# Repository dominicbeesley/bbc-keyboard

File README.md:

# bbc-keyboard
A bbc micro external keyboard

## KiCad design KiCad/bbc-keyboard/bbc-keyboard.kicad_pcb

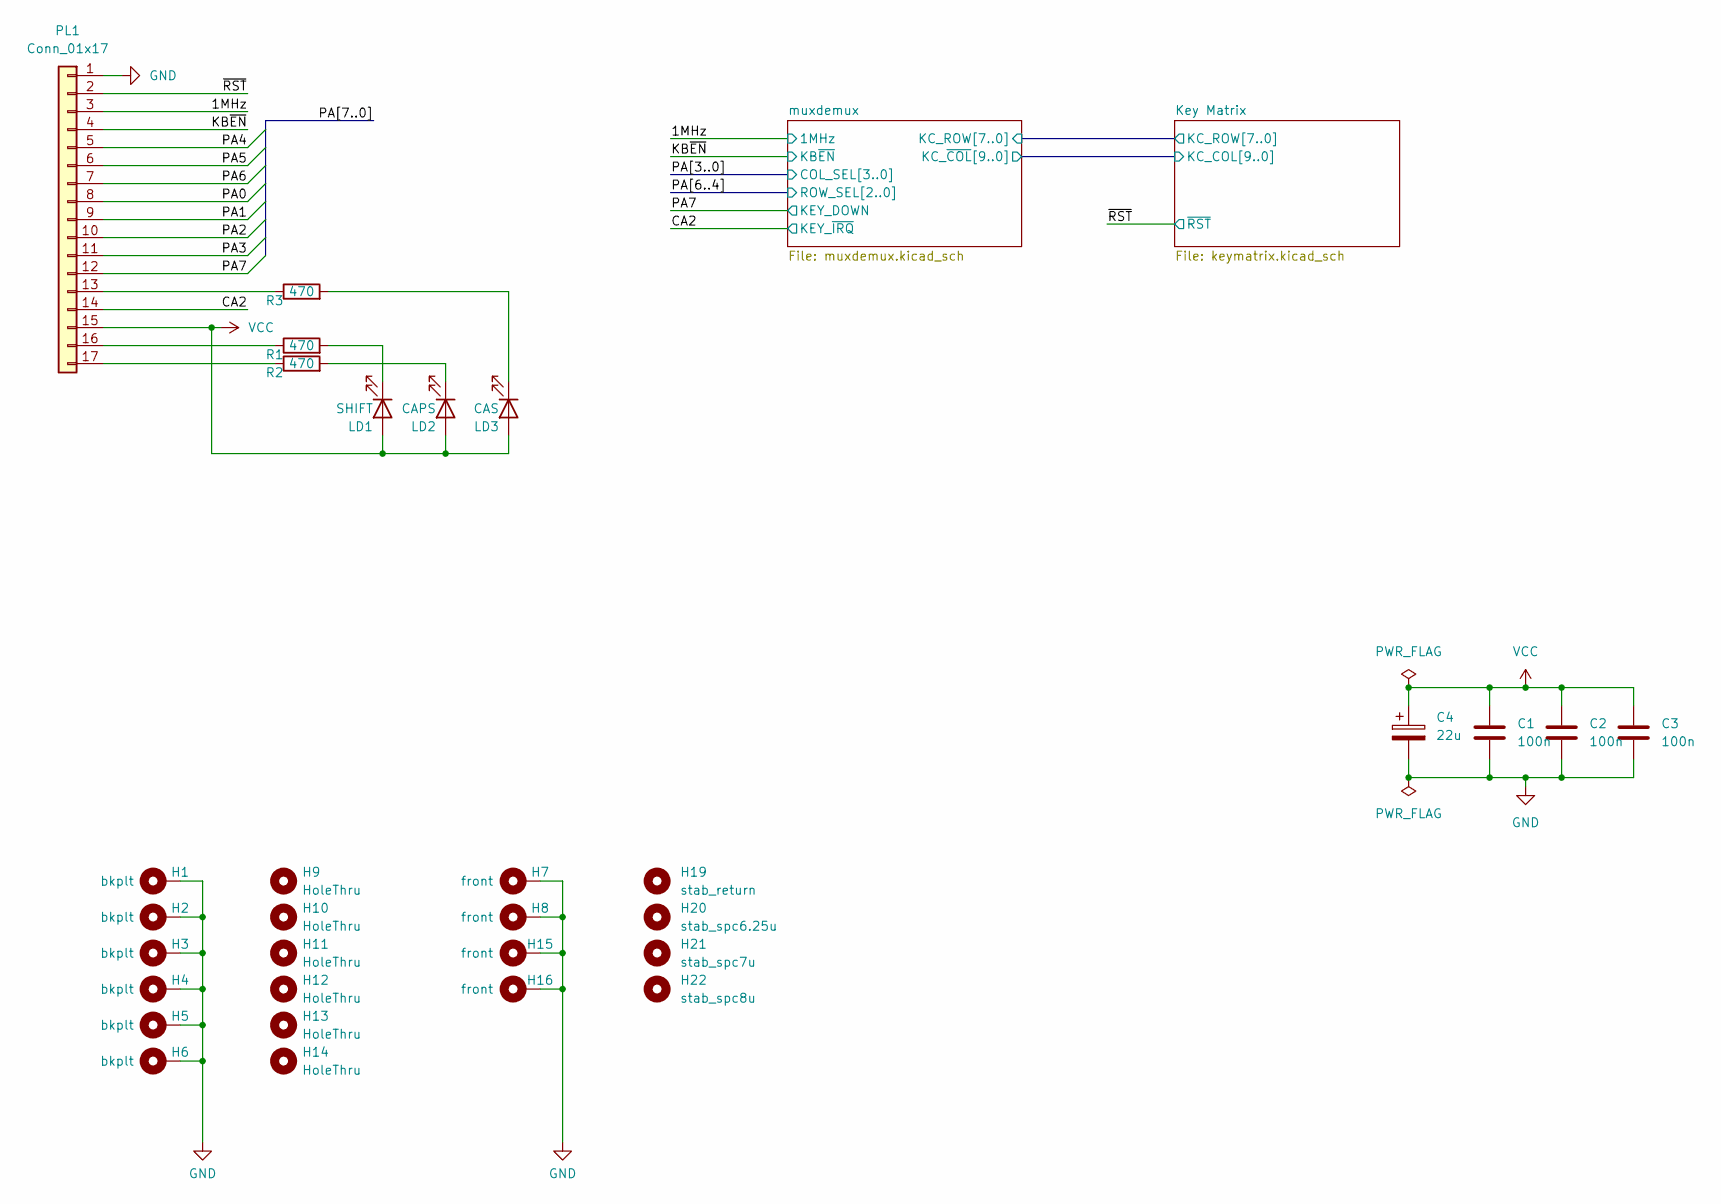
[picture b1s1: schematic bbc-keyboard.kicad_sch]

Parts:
C1, C2, C3: 100n; C_Disc_D9.0mm_W2.5mm_P5.00mm
C4: 22u; CP_Radial_D5.0mm_P2.00mm
H1, H2, H3, H4, H5, H6: bkplt; MountingHole_3.2mm_M3_DIN965_Pad
H7, H8: front; MountingHole_3.2mm_M3_DIN965_Pad
H9, H10, H11, H12, H13, H14: HoleThru; SquareHole_6.5mm
H15, H16: front; MountingHole_2.7mm_M2.5_DIN965_Pad
H19: stab_return; Stabilizer_Cherry_MX_2.00u
H20: stab_spc6.25u; Stabilizer_Cherry_MX_6.25u
H21: stab_spc7u; Stabilizer_Cherry_MX_7.00u
H22: stab_spc8u; Stabilizer_Cherry_MX_8.00u
LD1: SHIFT; LED_D5.0mm
LD2: CAPS; LED_D5.0mm
LD3: CAS; LED_D5.0mm
PL1: Conn_01x17; PinHeader_1x17_P2.54mm_Horizontal_noSilk
R1, R2, R3: 470; R_Axial_DIN0309_L9.0mm_D3.2mm_P12.70mm_Horizontal

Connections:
/1MHz: PL1.3; also elsewhere on the board
/CA2: PL1.14; also elsewhere on the board
/KB~EN: PL1.4; also elsewhere on the board
/PA0: PL1.8; also elsewhere on the board
/PA1: PL1.9; also elsewhere on the board
/PA2: PL1.10; also elsewhere on the board
/PA3: PL1.11; also elsewhere on the board
/PA4: PL1.5; also elsewhere on the board
/PA5: PL1.6; also elsewhere on the board
/PA6: PL1.7; also elsewhere on the board
/PA7: PL1.12; also elsewhere on the board
/~RST: PL1.2; also elsewhere on the board
GND: C1.2, C2.2, C3.2, C4.2, H1.1, H2.1, H3.1, H4.1, H5.1, H6.1, H7.1, H8.1, H15.1, H16.1, PL1.1; also elsewhere on the board
unnamed: LD1.1 (K), R1.2
unnamed: LD2.1 (K), R2.2
unnamed: LD3.1 (K), R3.2
unnamed: PL1.13, R3.1
unnamed: PL1.16, R1.1
unnamed: PL1.17, R2.1
VCC: C1.1, C2.1, C3.1, C4.1, LD1.2 (A), LD2.2 (A), LD3.2 (A), PL1.15; also elsewhere on the board

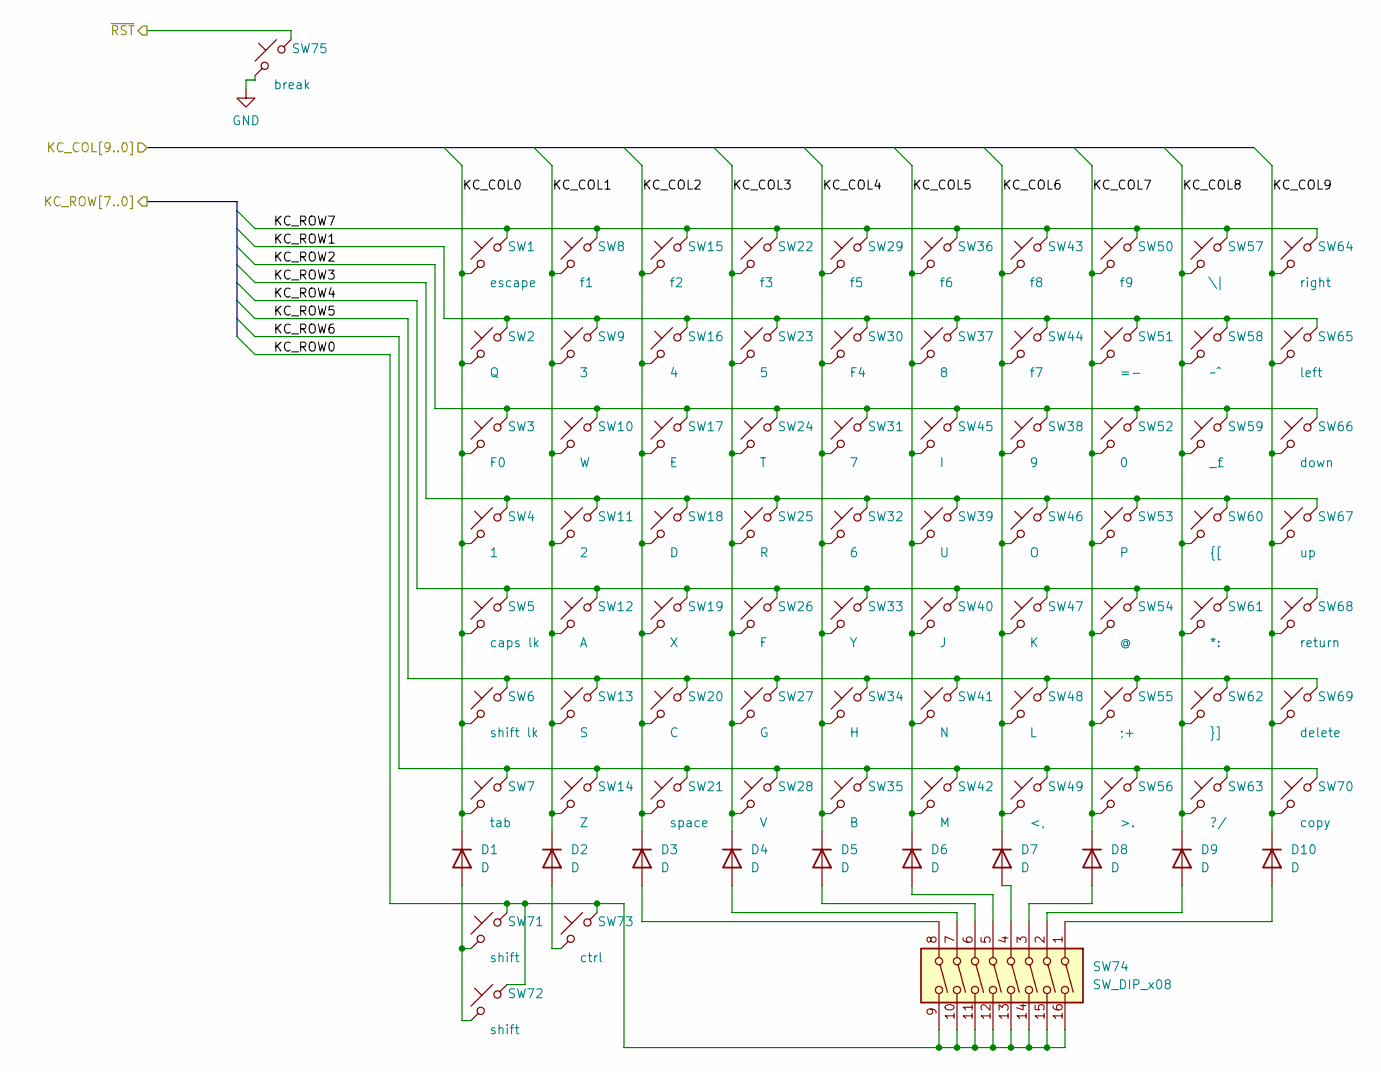
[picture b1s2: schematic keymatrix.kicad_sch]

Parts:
D1, D2, D3, D4, D5, D6, D7, D8, D9, D10: D; D_DO-34_SOD68_P10.16mm_Horizontal
SW1: escape; SW_Cherry_MX_PCB_1.00u
SW2: Q; SW_Cherry_MX_PCB_1.00u
SW3: F0; SW_Cherry_MX_PCB_1.00u
SW4: 1; SW_Cherry_MX_PCB_1.00u
SW5: caps lk; SW_Cherry_MX_PCB_1.00u
SW6: shift lk; SW_Cherry_MX_PCB_1.00u
SW7: tab; SW_Cherry_MX_PCB_1.50u
SW8: f1; SW_Cherry_MX_PCB_1.00u
SW9: 3; SW_Cherry_MX_PCB_1.00u
SW10: W; SW_Cherry_MX_PCB_1.00u
SW11: 2; SW_Cherry_MX_PCB_1.00u
SW12: A; SW_Cherry_MX_PCB_1.00u
SW13: S; SW_Cherry_MX_PCB_1.00u
SW14: Z; SW_Cherry_MX_PCB_1.00u
SW15: f2; SW_Cherry_MX_PCB_1.00u
SW16: 4; SW_Cherry_MX_PCB_1.00u
SW17: E; SW_Cherry_MX_PCB_1.00u
SW18: D; SW_Cherry_MX_PCB_1.00u
SW19: X; SW_Cherry_MX_PCB_1.00u
SW20: C; SW_Cherry_MX_PCB_1.00u
SW21: space; SW_Cherry_MX_PCB_6.50u
SW22: f3; SW_Cherry_MX_PCB_1.00u
SW23: 5; SW_Cherry_MX_PCB_1.00u
SW24: T; SW_Cherry_MX_PCB_1.00u
SW25: R; SW_Cherry_MX_PCB_1.00u
SW26: F; SW_Cherry_MX_PCB_1.00u
SW27: G; SW_Cherry_MX_PCB_1.00u
SW28: V; SW_Cherry_MX_PCB_1.00u
SW29: f5; SW_Cherry_MX_PCB_1.00u
SW30: F4; SW_Cherry_MX_PCB_1.00u
SW31: 7; SW_Cherry_MX_PCB_1.00u
SW32: 6; SW_Cherry_MX_PCB_1.00u
SW33: Y; SW_Cherry_MX_PCB_1.00u
SW34: H; SW_Cherry_MX_PCB_1.00u
SW35: B; SW_Cherry_MX_PCB_1.00u
SW36: f6; SW_Cherry_MX_PCB_1.00u
SW37: 8; SW_Cherry_MX_PCB_1.00u
SW38: 9; SW_Cherry_MX_PCB_1.00u
SW39: U; SW_Cherry_MX_PCB_1.00u
SW40: J; SW_Cherry_MX_PCB_1.00u
SW41: N; SW_Cherry_MX_PCB_1.00u
SW42: M; SW_Cherry_MX_PCB_1.00u
SW43: f8; SW_Cherry_MX_PCB_1.00u
SW44: f7; SW_Cherry_MX_PCB_1.00u
SW45: I; SW_Cherry_MX_PCB_1.00u
SW46: O; SW_Cherry_MX_PCB_1.00u
SW47: K; SW_Cherry_MX_PCB_1.00u
SW48: L; SW_Cherry_MX_PCB_1.00u
SW49: <,; SW_Cherry_MX_PCB_1.00u
SW50: f9; SW_Cherry_MX_PCB_1.00u
SW51: =-; SW_Cherry_MX_PCB_1.00u
SW52: 0; SW_Cherry_MX_PCB_1.00u
SW53: P; SW_Cherry_MX_PCB_1.00u
SW54: @; SW_Cherry_MX_PCB_1.00u
SW55: ;+; SW_Cherry_MX_PCB_1.00u
SW56: >.; SW_Cherry_MX_PCB_1.00u
SW57: \|; SW_Cherry_MX_PCB_1.00u
SW58: ~^; SW_Cherry_MX_PCB_1.00u
SW59: _£; SW_Cherry_MX_PCB_1.00u
SW60: {[; SW_Cherry_MX_PCB_1.00u
SW61: *:; SW_Cherry_MX_PCB_1.00u
SW62: }]; SW_Cherry_MX_PCB_1.00u
SW63: ?/; SW_Cherry_MX_PCB_1.00u
SW64: right; SW_Cherry_MX_PCB_1.00u
SW65: left; SW_Cherry_MX_PCB_1.00u
SW66: down; SW_Cherry_MX_PCB_1.00u
SW67: up; SW_Cherry_MX_PCB_1.00u
SW68: return; SW_Cherry_MX_PCB_2.00u
SW69: delete; SW_Cherry_MX_PCB_1.00u
SW70: copy; SW_Cherry_MX_PCB_1.00u
SW71, SW72: shift; SW_Cherry_MX_PCB_1.50u
SW73: ctrl; SW_Cherry_MX_PCB_1.00u
SW74: SW_DIP_x08; SW_DIP_SPSTx08_Slide_9.78x22.5mm_W7.62mm_P2.54mm
SW75: break; SW_Cherry_MX_PCB_1.00u

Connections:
/Key Matrix/KC_COL0: D1.1 (K), SW1.1, SW2.1, SW3.1, SW4.1, SW5.1, SW6.1, SW7.1; also elsewhere on the board
/Key Matrix/KC_COL1: D2.1 (K), SW8.1, SW9.1, SW10.1, SW11.1, SW12.1, SW13.1, SW14.1; also elsewhere on the board
/Key Matrix/KC_COL2: D3.1 (K), SW15.1, SW16.1, SW17.1, SW18.1, SW19.1, SW20.1, SW21.1; also elsewhere on the board
/Key Matrix/KC_COL3: D4.1 (K), SW22.1, SW23.1, SW24.1, SW25.1, SW26.1, SW27.1, SW28.1; also elsewhere on the board
/Key Matrix/KC_COL4: D5.1 (K), SW29.1, SW30.1, SW31.1, SW32.1, SW33.1, SW34.1, SW35.1; also elsewhere on the board
/Key Matrix/KC_COL5: D6.1 (K), SW36.1, SW37.1, SW39.1, SW40.1, SW41.1, SW42.1, SW45.1; also elsewhere on the board
/Key Matrix/KC_COL6: D7.1 (K), SW38.1, SW43.1, SW44.1, SW46.1, SW47.1, SW48.1, SW49.1; also elsewhere on the board
/Key Matrix/KC_COL7: D8.1 (K), SW50.1, SW51.1, SW52.1, SW53.1, SW54.1, SW55.1, SW56.1; also elsewhere on the board
/Key Matrix/KC_COL8: D9.1 (K), SW57.1, SW58.1, SW59.1, SW60.1, SW61.1, SW62.1, SW63.1; also elsewhere on the board
/Key Matrix/KC_COL9: D10.1 (K), SW64.1, SW65.1, SW66.1, SW67.1, SW68.1, SW69.1, SW70.1; also elsewhere on the board
/Key Matrix/KC_ROW0: SW71.2, SW72.2, SW73.2, SW74.9, SW74.10, SW74.11, SW74.12, SW74.13, SW74.14, SW74.15, SW74.16; also elsewhere on the board
/Key Matrix/KC_ROW1: SW2.2, SW9.2, SW16.2, SW23.2, SW30.2, SW37.2, SW44.2, SW51.2, SW58.2, SW65.2; also elsewhere on the board
/Key Matrix/KC_ROW2: SW3.2, SW10.2, SW17.2, SW24.2, SW31.2, SW38.2, SW45.2, SW52.2, SW59.2, SW66.2; also elsewhere on the board
/Key Matrix/KC_ROW3: SW4.2, SW11.2, SW18.2, SW25.2, SW32.2, SW39.2, SW46.2, SW53.2, SW60.2, SW67.2; also elsewhere on the board
/Key Matrix/KC_ROW4: SW5.2, SW12.2, SW19.2, SW26.2, SW33.2, SW40.2, SW47.2, SW54.2, SW61.2, SW68.2; also elsewhere on the board
/Key Matrix/KC_ROW5: SW6.2, SW13.2, SW20.2, SW27.2, SW34.2, SW41.2, SW48.2, SW55.2, SW62.2, SW69.2; also elsewhere on the board
/Key Matrix/KC_ROW6: SW7.2, SW14.2, SW21.2, SW28.2, SW35.2, SW42.2, SW49.2, SW56.2, SW63.2, SW70.2; also elsewhere on the board
/Key Matrix/KC_ROW7: SW1.2, SW8.2, SW15.2, SW22.2, SW29.2, SW36.2, SW43.2, SW50.2, SW57.2, SW64.2; also elsewhere on the board
/~RST: SW75.2; also elsewhere on the board
GND: SW75.1; also elsewhere on the board
unnamed: D1.2 (A), SW71.1, SW72.1
unnamed: D2.2 (A), SW73.1
unnamed: D3.2 (A), SW74.8
unnamed: D4.2 (A), SW74.7
unnamed: D5.2 (A), SW74.6
unnamed: D6.2 (A), SW74.5
unnamed: D7.2 (A), SW74.4
unnamed: D8.2 (A), SW74.3
unnamed: D9.2 (A), SW74.2
unnamed: D10.2 (A), SW74.1

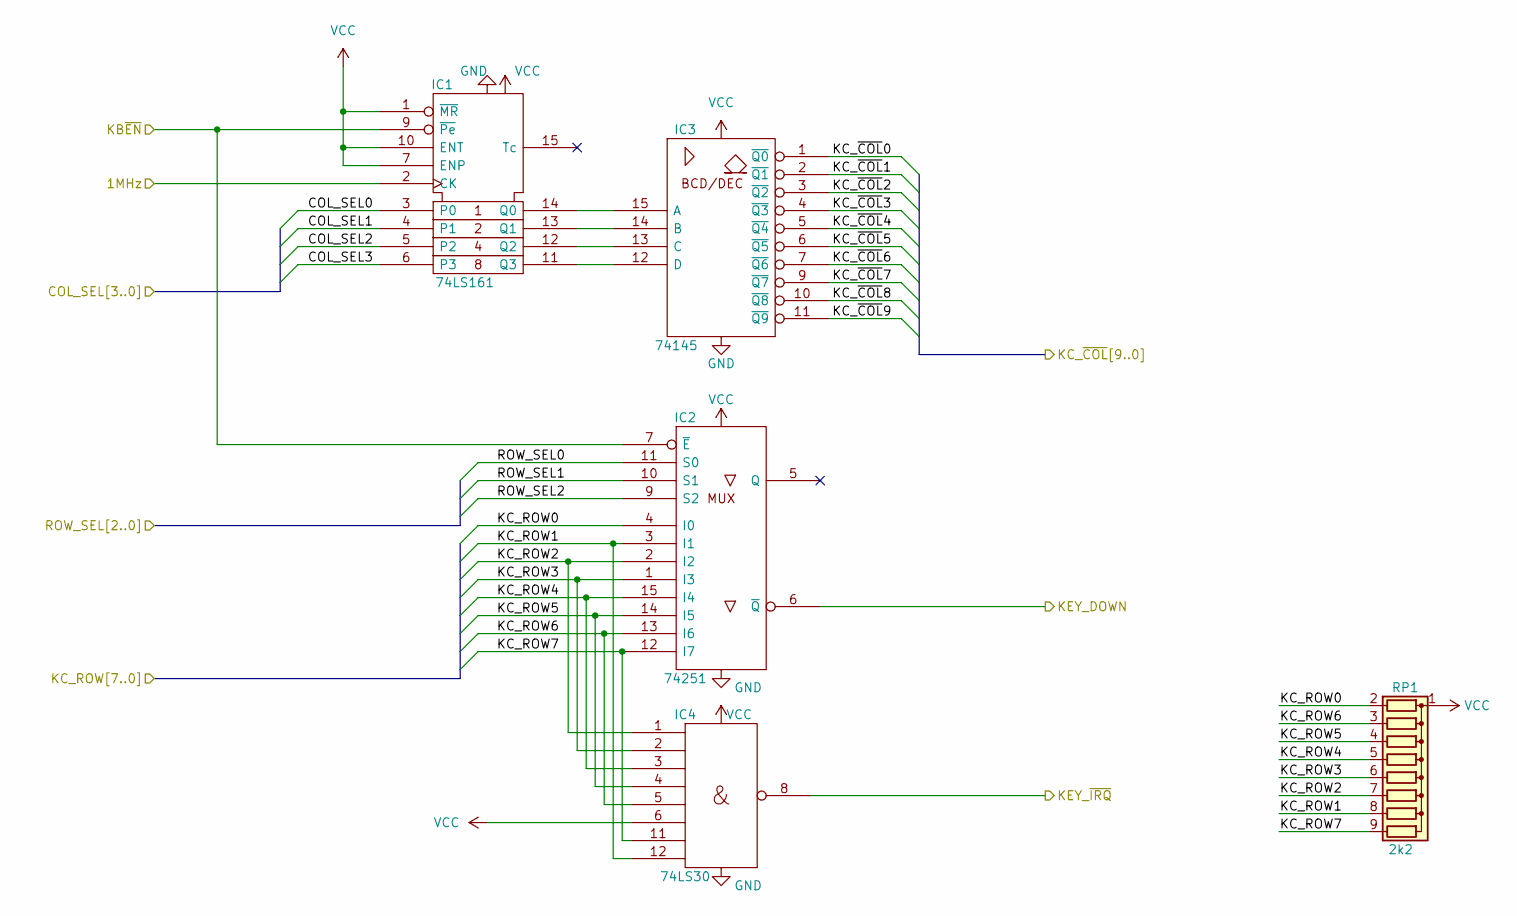
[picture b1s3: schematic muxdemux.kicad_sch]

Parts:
IC1: 74LS161; DIP-16_W7.62mm
IC2: 74251; DIP-16_W7.62mm
IC3: 74145; DIP-16_W7.62mm
IC4: 74LS30; DIP-14_W7.62mm
RP1: 2k2; R_Array_SIP9

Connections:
/1MHz: IC1.2 (CK); also elsewhere on the board
/CA2: IC4.8; also elsewhere on the board
/KB~EN: IC1.9 (~Pe), IC2.7 (~E); also elsewhere on the board
/Key Matrix/KC_COL0: IC3.1 (~Q0); also elsewhere on the board
/Key Matrix/KC_COL1: IC3.2 (~Q1); also elsewhere on the board
/Key Matrix/KC_COL2: IC3.3 (~Q2); also elsewhere on the board
/Key Matrix/KC_COL3: IC3.4 (~Q3); also elsewhere on the board
/Key Matrix/KC_COL4: IC3.5 (~Q4); also elsewhere on the board
/Key Matrix/KC_COL5: IC3.6 (~Q5); also elsewhere on the board
/Key Matrix/KC_COL6: IC3.7 (~Q6); also elsewhere on the board
/Key Matrix/KC_COL7: IC3.9 (~Q7); also elsewhere on the board
/Key Matrix/KC_COL8: IC3.10 (~Q8); also elsewhere on the board
/Key Matrix/KC_COL9: IC3.11 (~Q9); also elsewhere on the board
/Key Matrix/KC_ROW0: IC2.4 (I0), RP1.2 (R1); also elsewhere on the board
/Key Matrix/KC_ROW1: IC2.3 (I1), IC4.12, RP1.8 (R7); also elsewhere on the board
/Key Matrix/KC_ROW2: IC2.2 (I2), IC4.1, RP1.7 (R6); also elsewhere on the board
/Key Matrix/KC_ROW3: IC2.1 (I3), IC4.2, RP1.6 (R5); also elsewhere on the board
/Key Matrix/KC_ROW4: IC2.15 (I4), IC4.3, RP1.5 (R4); also elsewhere on the board
/Key Matrix/KC_ROW5: IC2.14 (I5), IC4.4, RP1.4 (R3); also elsewhere on the board
/Key Matrix/KC_ROW6: IC2.13 (I6), IC4.5, RP1.3 (R2); also elsewhere on the board
/Key Matrix/KC_ROW7: IC2.12 (I7), IC4.11, RP1.9 (R8); also elsewhere on the board
/PA0: IC1.3 (P0); also elsewhere on the board
/PA1: IC1.4 (P1); also elsewhere on the board
/PA2: IC1.5 (P2); also elsewhere on the board
/PA3: IC1.6 (P3); also elsewhere on the board
/PA4: IC2.11 (S0); also elsewhere on the board
/PA5: IC2.10 (S1); also elsewhere on the board
/PA6: IC2.9 (S2); also elsewhere on the board
/PA7: IC2.6 (~Q); also elsewhere on the board
GND: IC1.8 (GND), IC2.8 (GND), IC3.8 (GND), IC4.7 (Gnd); also elsewhere on the board
unnamed: IC1.11 (Q3), IC3.12 (D)
unnamed: IC1.12 (Q2), IC3.13 (C)
unnamed: IC1.13 (Q1), IC3.14 (B)
unnamed: IC1.14 (Q0), IC3.15 (A)
VCC: IC1.1 (~MR), IC1.7 (ENP), IC1.10 (ENT), IC1.16 (VCC), IC2.16 (VCC), IC3.16 (VCC), IC4.6, IC4.14 (Vcc), RP1.1 (common); also elsewhere on the board

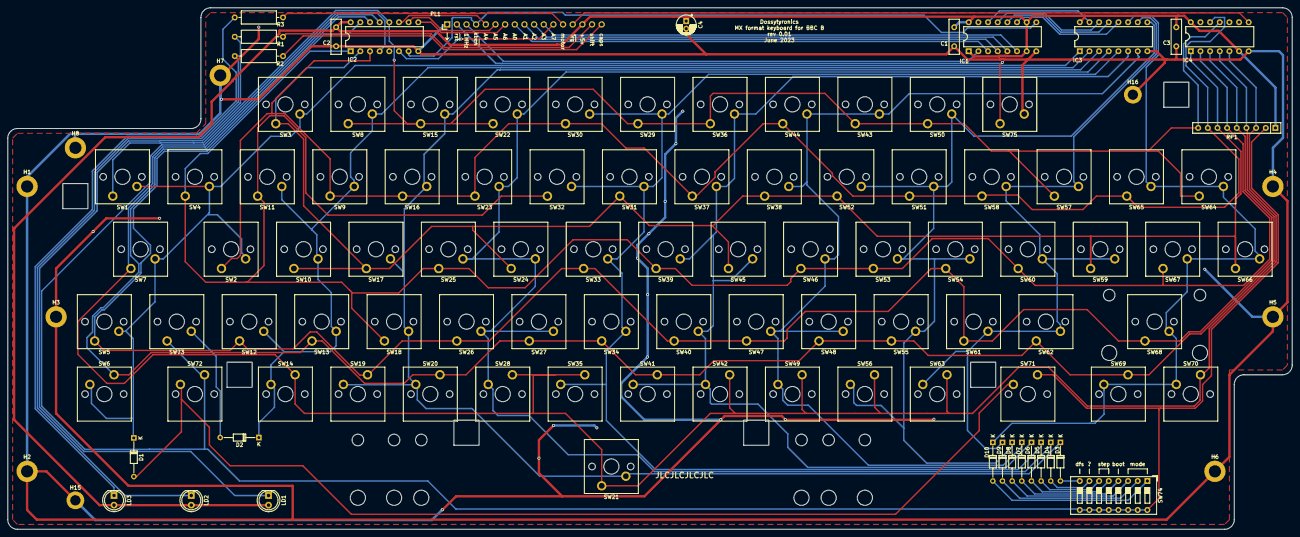
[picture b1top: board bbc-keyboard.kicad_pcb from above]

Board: 2 copper layers, 337.8 x 137.2 mm, 121 parts (0 on the bottom side), 52 nets.

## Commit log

2023-06-24 Create LICENSE
2023-06-24 new project
2023-06-24 schema
2023-06-24 1st cut mux/demux
2023-06-24 muxdemux irq det
2023-06-24 Fix up ERC
2023-06-24 pull ups
2023-06-24 Break Key
2023-06-25 All keys laid out
2023-06-25 draw 1st cut retainer plate outline
2023-06-25 Added - original outlines
2023-06-25 missing .sch updates
2023-06-25 LEDs
2023-06-25 placing components
2023-06-25 start some routing
2023-06-25 rotate switches 180 degrees
2023-06-25 start routing
2023-06-26 routed rhs
2023-06-26 tidy routing
2023-06-26 more layout tidying
2023-06-26 DRC pass
2023-06-26 Add stabilizer for space
2023-06-26 return stabilizers
2023-06-28 mounting holes for backplates
2023-06-30 mounting holes
2023-06-30 remove a ruler
2023-06-30 mounting holes, symbols for stabilizers
2023-06-30 route to extra mounting holes
2023-06-30 Silkscreen violations on stab bars
2023-06-30 silkscreen and tidying
2023-06-30 tidy up routing
2023-06-30 rounded corners
2023-06-30 Front copper fill
2023-06-30 Back copper fill
2023-07-03 move rp1 to avoid mounting point
2023-07-03 rotate bottom row switches to avoid fouling backrail
2023-07-03 Start front plate, remove H17, H18 pcb to front near space
2023-07-03 move H7
2023-07-03 front plate edge cuts
2023-07-03 LED holes
2023-07-03 stabilizer bar holes
2023-07-04 remove silkscreen text
2023-07-04 1st go fab plots, fix missing fill area
2023-07-04 Updated fab plots
2023-07-05 Corrected fab plots (and jlc marker) - feedback from jlc support
2023-10-16 Tweak measurements on left ear, add speaker mounting holes
2023-10-16 enlarge mounting holes on main pcb
2023-10-16 remove line up sketches
2023-10-16 Enlarge mounting holes and fix up ears templates to match main pcb
2023-10-16 Lock everything
2023-10-16 enlarge holes and match up to main pcb
2023-10-16 NEW: left ear
2023-10-16 Ooops - didn't save, include correct mounting holes
2023-10-16 FIX: ghost outline tweak
2023-10-16 NEW: right ear
2023-10-16 Fabrication files
2024-01-26 FIX: mounting holes larger
2024-06-06 FIX: I/9 were swapped blame AUG
2024-06-06 reposition resistor pack to avoid fouling IC - still under front-plate
2024-06-06 rotate C4 - allow bend horizontally
2024-06-06 increase clearance around diode array
2024-06-06 larger LED holes, remove silkscreen designators
    update LED holes in schematic
    larger LED holes, remove silkscreens
2024-06-06 zone fills, routing tweak
